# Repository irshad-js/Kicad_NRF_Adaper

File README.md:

# Kicad_NRF_Adaper
PCB adapter for NRF52832 using Kicad

Project updated to version 2.0 

Please wait for bug status of the hardware.

Project made possible by the help of Dr. Peter Dalmaris with his Udemy course "KiCad Like a Pro 2nd edition". This course is highly recommended.

PCB front side:

PCB back side:

Module front:

Hardware picture 1:

Hardware picture 2:

Hardware picture 3:

Hardware picture 4:

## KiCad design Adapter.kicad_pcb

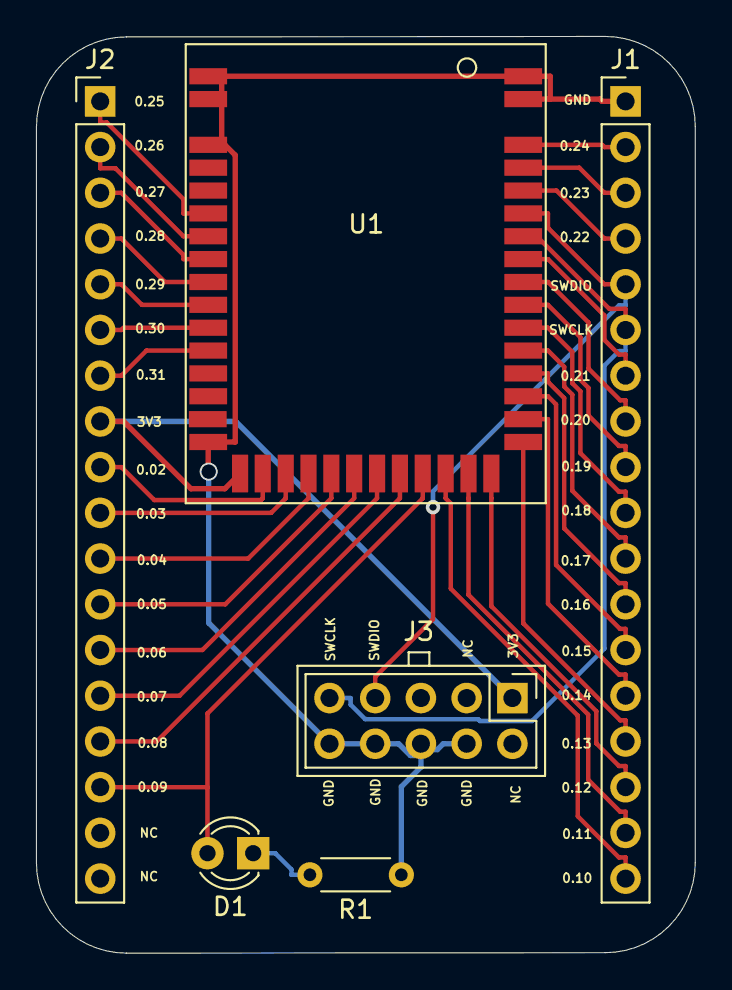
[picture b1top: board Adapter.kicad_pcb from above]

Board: 2 copper layers, 36.6 x 50.9 mm, 6 parts (0 on the bottom side), 35 nets.

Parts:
D1: LED; LED_D3.0mm
J1, J2: Conn_01x18; PinHeader_1x18_P2.54mm_Vertical
J3: Conn_02x05_Odd_Even; PinHeader_2x05_P2.54mm_Vertical
R1: R; R_Axial_DIN0204_L3.6mm_D1.6mm_P5.08mm_Horizontal
U1: NRF52832_E73-2G4M04S1B; NRF52832_E73-2G4M04S1B_SMD

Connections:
/6: J2.1, U1.6
/7: J2.2, U1.7
/8: J2.3, U1.8
/9: J2.4, U1.9
/10: J2.5, U1.10
/11: J2.6, U1.11
/12: J2.7, U1.12
/18: J2.9, U1.18
/19: J2.10, U1.19
/20: J2.11, U1.20
/21: J2.12, U1.21
/22: J2.13, U1.22
/23: J2.14, U1.23
/24: J2.15, U1.24
/25: D1.2, J2.16, U1.25
/26: J1.18, U1.26
/27: J1.17, U1.27
/28: J1.16, U1.28
/29: J1.15, U1.29
/30: J1.14, U1.30
/31: J1.13, U1.31
/32: J1.12, U1.32
/33: J1.11, U1.33
/34: J1.10, U1.34
/35: J1.9, U1.35
/36: J1.8, U1.36
/37: J1.7, U1.37
/38: J1.6, J3.9, U1.38
/39: J1.5, J3.7, U1.39
/40: J1.4, U1.40
/41: J1.3, U1.41
/42: J1.2, U1.42
/+3.3VCC: J2.8, J3.1, U1.17
GND: J1.1, J3.4, J3.6, J3.8, J3.10, R1.1, U1.1, U1.2, U1.3, U1.16, U1.43, U1.44
unnamed: D1.1, R1.2

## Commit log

2020-07-24 First commit to initialize and store the available project.
    Do not use this commit as the hardware is flipped with respect to specification.
    Wait for the next commit/version.
2020-07-25 Version 2.0 updated.
    PCB design updated.
2020-07-25 Drill files added
2020-08-31 Added hardware pictures.
